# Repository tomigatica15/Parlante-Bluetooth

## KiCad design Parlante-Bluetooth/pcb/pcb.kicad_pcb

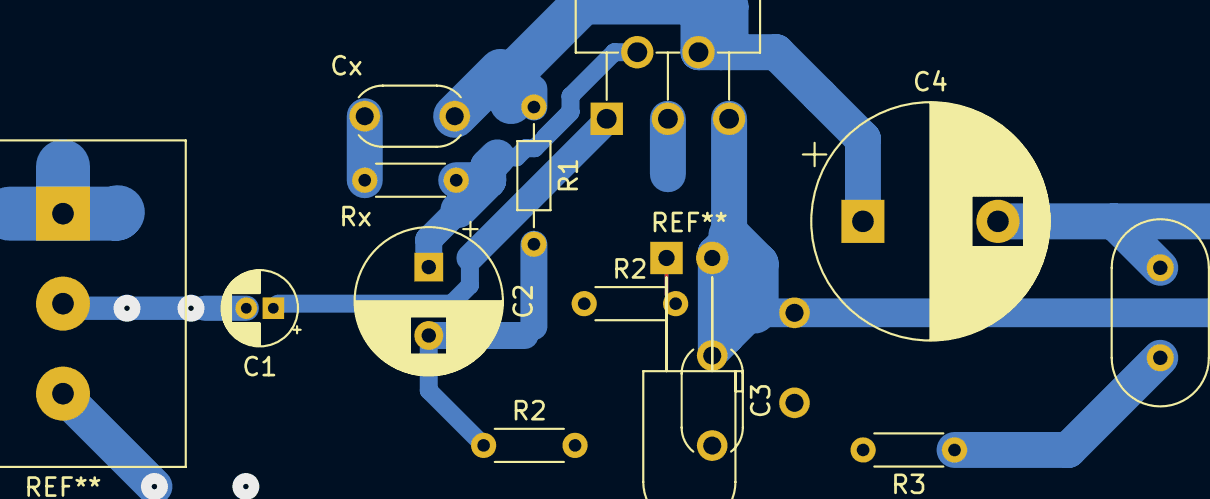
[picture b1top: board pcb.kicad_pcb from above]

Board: 2 copper layers, 12 parts (0 on the bottom side), 9 nets.

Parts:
C1: 10uF; CP_Radial_D4.0mm_P1.50mm
C2: 470uF; CP_Radial_D8.0mm_P3.80mm
C3: 100nF; Resonator-2Pin_W6.0mm_H3.0mm
C4: 2200uF; CP_Radial_D13.0mm_P7.50mm
C5: 100nF; Resonator-2Pin_W10.0mm_H5.0mm
Cx: 68nF; Resonator-2Pin_W6.0mm_H3.0mm
R1: 120; R_Axial_DIN0204_L3.6mm_D1.6mm_P7.62mm_Horizontal
R2, R2#2: 4; R_Axial_DIN0204_L3.6mm_D1.6mm_P5.08mm_Horizontal
R3: 1; R_Axial_DIN0204_L3.6mm_D1.6mm_P5.08mm_Horizontal
Rx: 100; R_Axial_DIN0204_L3.6mm_D1.6mm_P5.08mm_Horizontal
U1: TDA2003; TO-220-5_P3.4x3.7mm_StaggerOdd_Lead3.8mm_Vertical

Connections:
+12V: C3.1, U1.5 (V+)
GND: C3.2, R2#2.2, R3.2, U1.3 (GND)
unnamed: C2.2, R1.2, R2#2.1
unnamed: C4.1, Cx.1, R1.1, U1.4
unnamed: C4.2, C5.1
unnamed: C5.2, R3.1
unnamed: Cx.2, Rx.1
unnamed: C1.1, U1.1 (+)
unnamed: C2.1, Rx.2, U1.2 (-)
